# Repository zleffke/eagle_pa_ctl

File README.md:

# eagle_pa_ctl
EagleCAD PA control boards

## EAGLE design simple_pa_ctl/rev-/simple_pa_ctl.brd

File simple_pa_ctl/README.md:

# Simple Power Amplifier Control Board
Simple Control Board for RF Power Amplifier.

Design Features:
* USB interface
* Reads FWD/REV power levels from Dual Directional Coupler (in this case bird wattmeter)
* Monitors DC power consumption
* Monitors Power Amplifier Temperature
* Monitors Board Temperature
* Monitors Thermostat (digital indicator)
* Controls PA Module relay
* Controls Fan
* Based on ATMEGA32U4 microcontroller.  Initial design utilizes Arduino Feather firmware load that emulates an Adafruit Feather32u4

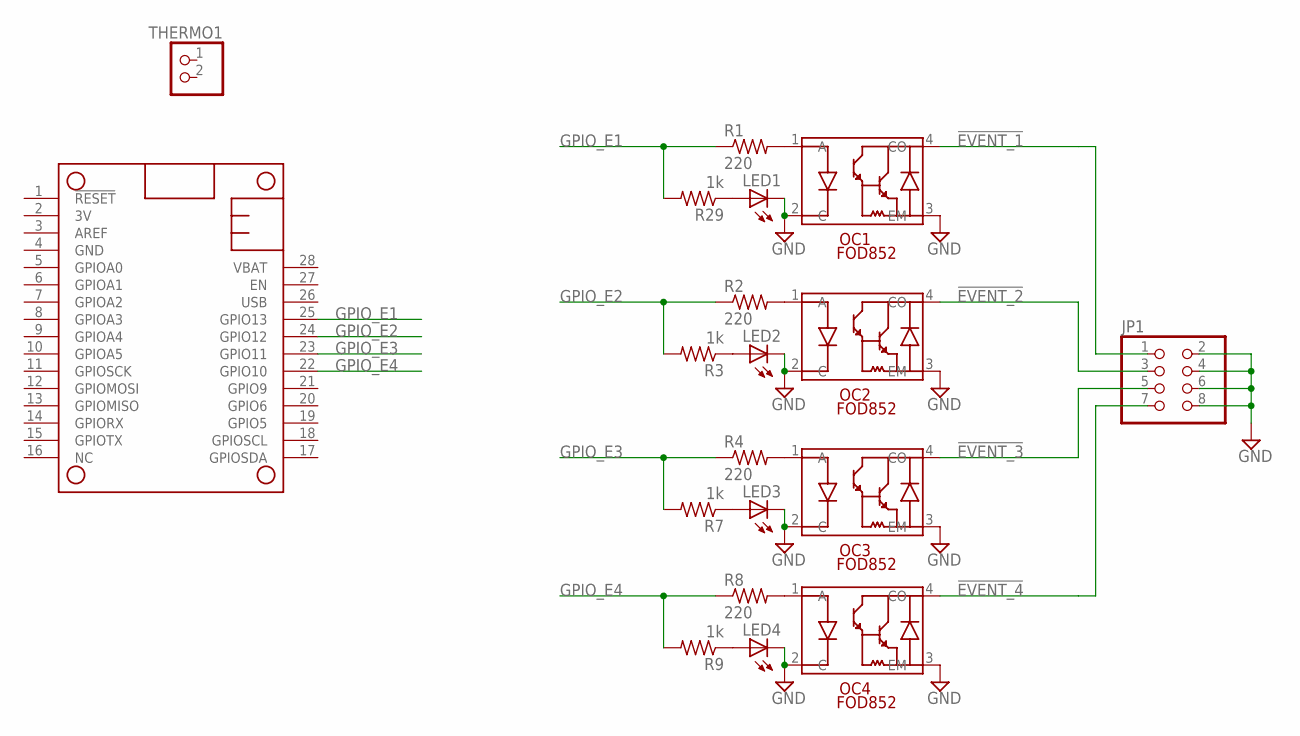
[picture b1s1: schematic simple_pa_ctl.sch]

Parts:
JP1: PINHD-2X4; 2X04
LED1, LED2, LED3, LED4: LEDCHIPLED_0805; CHIPLED_0805
MS1: FEATHERWING
OC1, OC2, OC3, OC4: FOD852; SMD4-7
R1, R2, R4, R8: 220; R0805
R3, R7, R9, R29: 1k; R0805
THERMO1: PINHD-1X2; 1X02

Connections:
!EVENT_1: JP1.1, OC1.4 (CO)
!EVENT_2: JP1.3, OC2.4 (CO)
!EVENT_3: JP1.5, OC3.4 (CO)
!EVENT_4: JP1.7, OC4.4 (CO)
GND: JP1.2, JP1.4, JP1.6, JP1.8, LED1.C, LED2.C, LED3.C, LED4.C, MS1.4 (GND), OC1.2 (C), OC1.3 (EM), OC2.2 (C), OC2.3 (EM), OC3.2 (C), OC3.3 (EM), OC4.2 (C), OC4.3 (EM)
GPIO_E1: MS1.25 (GPIO13), R1.1, R29.2
GPIO_E2: MS1.24 (GPIO12), R2.1, R3.2
GPIO_E3: MS1.23 (GPIO11), R4.1, R7.2
GPIO_E4: MS1.22 (GPIO10), R8.1, R9.2
unnamed: OC1.1 (A), R1.2
unnamed: LED1.A, R29.1
unnamed: OC2.1 (A), R2.2
unnamed: LED2.A, R3.1
unnamed: OC3.1 (A), R4.2
unnamed: LED3.A, R7.1
unnamed: OC4.1 (A), R8.2
unnamed: LED4.A, R9.1

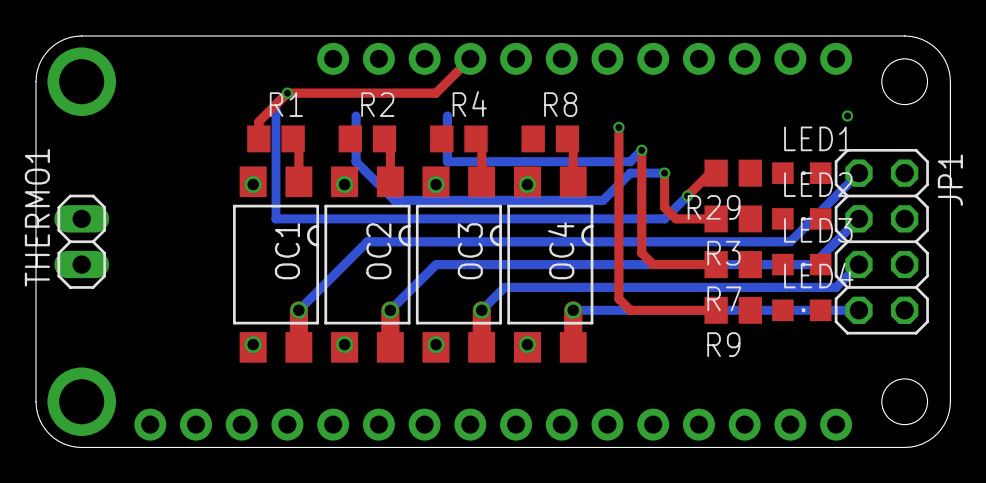
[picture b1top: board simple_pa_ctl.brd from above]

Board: 2 copper layers, 50.8 x 22.9 mm, 19 parts (0 on the bottom side), 17 nets.

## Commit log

2018-09-01 Adding project README for simple PA control board
2018-09-02 initial mass commit. lots done with schematic, but a lot left to sort out and tweak. No boar dlayout done yet.
2018-10-22 very simple, featherwing footprint
2018-10-22 adding gitgnore
